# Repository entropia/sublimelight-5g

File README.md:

# sublimelight-5g

5th generation of illumination devices for Entropia e.V

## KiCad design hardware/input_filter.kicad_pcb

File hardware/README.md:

# sublimeilght-5g hardware

## known issues/gotchas

The pins in the footprint of the 3.3V regulator U5 are counted in the other direction compared to the 78-style regulators it replaces, but I used the 78-style kicad footprint there.
My solution was to replace the angeled pin header soldered to the module with a straight pin connector and then soldering U5 to the board so it points to the side of the PCB.
This also solves the possible issue that the levers of J8 aren't that far away from U5 when U5 is mounted at a 90 degree angle.

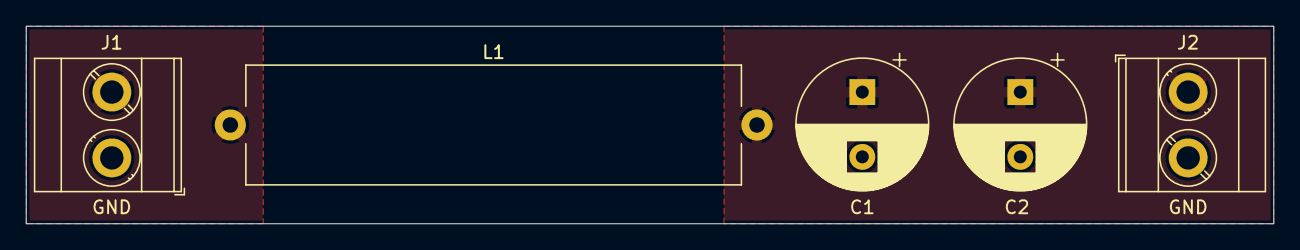
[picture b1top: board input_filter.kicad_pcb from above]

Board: 2 copper layers, 96.3 x 15.2 mm, 5 parts (0 on the bottom side), 3 nets, no tracks yet.

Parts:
C1, C2: EEU-FP1V511B; CP_Radial_D10.0mm_P5.00mm
J1, J2: Conn_01x02; TerminalBlock_Phoenix_MKDS-3-2-5.08_1x02_P5.08mm_Horizontal
L1: 5252-RC; R_Axial_Power_L38.0mm_W9.0mm_P40.64mm

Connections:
/V_IN: J1.2, L1.1
/V_OUT: C1.1, C2.1, J2.1, L1.2
GND: C1.2, C2.2, J1.1, J2.2

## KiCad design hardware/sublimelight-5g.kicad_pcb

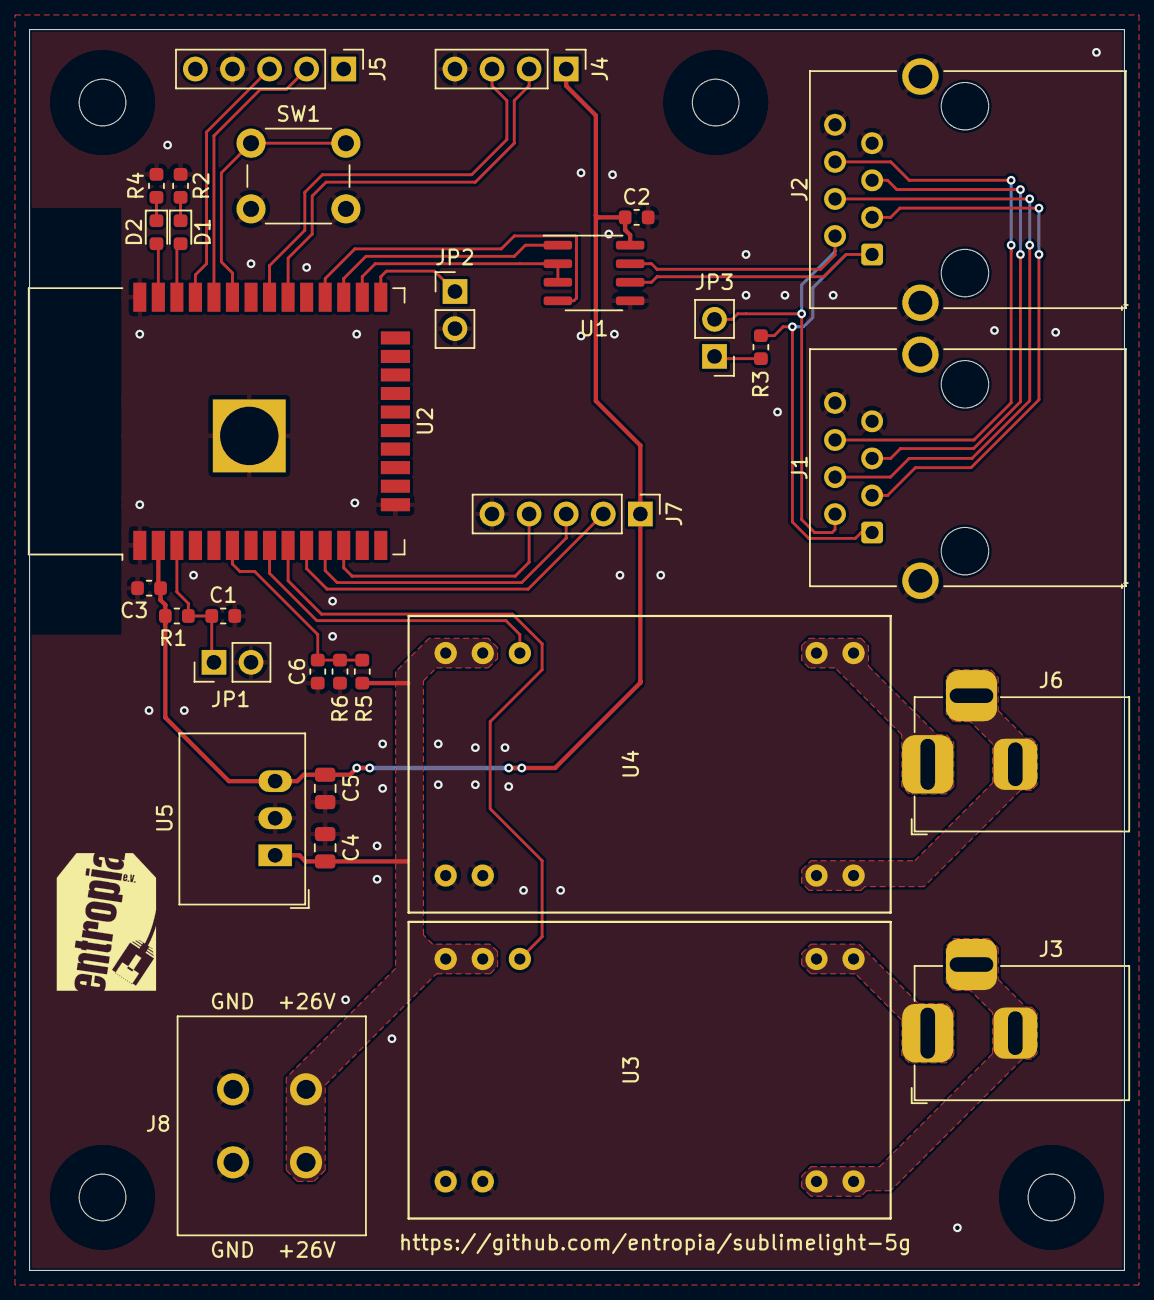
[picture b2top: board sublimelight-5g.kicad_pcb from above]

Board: 2 copper layers, 75.0 x 85.0 mm, 35 parts (0 on the bottom side), 34 nets.

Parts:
C1, C2, C3, C6: 100n; C_0603_1608Metric
C4: 10u; C_0805_2012Metric
C5: 22u; C_0805_2012Metric
D1, D2: LED; LED_0603_1608Metric
H1, H2, H3, H4: MountingHole; MountingHole_3.2mm_M3
J1, J2: RJ45; RJ45_MTJ-88TX1-FSD-PGB
J3, J6: Barrel_Jack_Switch; BarrelJack_Horizontal
J4: Conn_01x04; PinHeader_1x04_P2.54mm_Vertical
J5, J7: Conn_01x05; PinHeader_1x05_P2.54mm_Vertical
J8: Conn_01x02; TBL005A-500-02
JP1, JP2, JP3: Jumper_2_Open; PinHeader_1x02_P2.54mm_Vertical
R1, R6: 10k; R_0603_1608Metric
R2, R4: 1k; R_0603_1608Metric
R3: 120R; R_0603_1608Metric
R5: 100k; R_0603_1608Metric
SW1: SW_Push; SW_PUSH_6mm
U1: ST1480ACDR; SOIC-8_3.9x4.9mm_P1.27mm
U2: ESP32-WROOM-32D; ESP32-WROOM-32
U3, U4: LDD-H; LDD_H
U5: VXO7803-1000; Converter_DCDC_RECOM_R-78E-0.5_THT

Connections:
+3V3: C2.1, C3.1, C5.1, J4.1, J7.1, R1.1, U1.8, U2.2, U5.3
/AUX_0_0: J4.2, U2.30
/AUX_0_1: J4.3, U2.31
/AUX_1_0: J7.2, U2.10
/AUX_1_1: J7.3, U2.11
/AUX_1_2: J7.4, U2.12
/DI: U1.4, U2.28
/EN: C1.1, JP1.1, R1.2, U2.3
/IO0: JP2.1, U2.25
/LED0: D1.2, U2.36
/LED1: D2.2, U2.37
/PWM_W_COLD: U2.9, U3.22
/PWM_W_WARM: U2.8, U4.22
/RJ45_3: J1.3, J2.3
/RJ45_4: J1.4, J2.4
/RJ45_5: J1.5, J2.5
/RJ45_6: J1.6, J2.6
/RO: U1.1, U2.27
/RS485_A: J1.1, J2.1, R3.1, U1.6
/RS485_B: J1.2, J2.2, JP3.2, U1.7
/RTS: U1.2, U1.3, U2.26
/TASTER: SW1.1, U2.33
/USB_RXD: J5.3, U2.35
/USB_TXD: J5.2, U2.34
/V_SENSE: C6.1, R5.2, R6.1, U2.6
/W_COLD+: J3.1, U3.13, U3.14
/W_COLD-: J3.2, J3.3, U3.11, U3.12
/W_WARM+: J6.1, U4.13, U4.14
/W_WARM-: J6.2, J6.3, U4.11, U4.12
GND: C1.2, C2.2, C3.2, C4.2, C5.2, C6.2, J1.7, J1.8, J1.SH, J2.7, J2.8, J2.SH, J4.4, J5.4, J7.5, J8.1, JP1.2, JP2.2, R2.1, R4.1, R6.2, SW1.2, U1.5, U2.1, U2.15, U2.38, U2.39, U3.1, U3.2, U4.1, U4.2, U5.2
unnamed: D1.1, R2.2
unnamed: D2.1, R4.2
unnamed: JP3.1, R3.2
VCC: C4.1, J8.2, R5.1, U3.23, U3.24, U4.23, U4.24, U5.1

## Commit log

2019-10-19 add HW license
2019-10-19 move kicad gitignore to hardware folder
2019-10-19 add empty readme files
2019-10-19 add meanwell constant current led drivers
2019-10-19 create empty kicad project
2019-10-19 add meanwell constant current led driver to project
2019-10-20 add schematics backup file to gitignore
2019-10-20 begin hardware design
2019-10-20 add TBL005A-500-02 footprint
2019-10-24 add rj45 connector footprint
2019-10-24 first placement
2019-10-24 change net class parameters
2019-10-25 schematics mostly done; layout not finished yet
2019-10-26 route board
2019-10-26 add a little content to top-level readme
2019-10-26 add entropia logo
2019-10-26 add logo to board and clean up silkscreen
2019-10-29 sligthly change footprint of barel jack to match recommended footprint
2019-11-04 replace +28V power supply symbol with VCC symbol
    VCC is +26V
2019-11-16 add missing power flags in schematics
2019-11-16 add logos to board
2019-11-29 Imported Firmware-Skeleton
    From https://github.com/espressif/esp-idf-template.
2019-11-30 hardware/README.md: describe U5 problem/workaround
2020-01-01 Add LED test.
2020-01-01 Move test firmware to other directory, reset firmware to skeleton.
2020-01-02 Begin configuration web interface.
2020-01-05 WIP web interface.
2020-01-05 Update .gitignore for emacs.
2020-01-06 Finish web interface.
2020-01-06 Add necessary menuconfig adjustments.
2020-01-06 Add firmware update endpoint.
2020-01-07 Remove MQTT topic prefix setting, rename board_name -> device_name.
    We use the Tasmota convention for MQTT topics, so we simply include the
    device name in the topic.
2020-01-07 Remove default Wifi password.
2020-01-19 Hooray!
2020-02-21 Remove unneeded NULL check. free(NULL) is fine.
2020-02-21 Publish current IP address on stat/$device/IP.
2020-02-21 Delay rebooting after firmware update to enable HTTP response to be sent.
2020-02-21 Report git revision in web interface.
2020-02-22 Add prospective naming scheme.
2020-02-22 Add 3D model of power supply shroud (parameterized for both types of supply).
2020-02-28 hardware: add input LC denoise PCB
2020-03-01 Fix (?) generation of git_revision.h
2020-03-01 Honour configuration of broker URL instead of using hardcoded default.
    This means that after a config update we need to restart the MQTT client
    completely because we may need to connect to somewhere else. Given that
    config changes should be rare, we put no effort into restarting only when
    needed.
2020-03-01 Make fallback settings usably bright.
2020-03-05 Added publish functionality on light state change
2020-03-06 Fix memory leak and uninitialized local variable.
2020-03-09 Outsourced stat topic generation to topic_builder.c
2020-03-09 Remove obsolete variables
2020-03-09 Refactor MQTT receive handling to topic_builder
2020-03-21 Use statically allocated light_manager_state_t.
    Right now there is only ever one state object, so we have to need to
    allocate it on the heap.
2020-03-21 Make values in light_manager_state_t unsigned and not short.
    (a) It makes the types consistent with the API.
    (b) We don't need to save those four bytes.
2020-03-21 Add brightness and temperature settings to light_manager.
    This also requires more infrastructure to remember throwing all the
    required events. Withing the light manager, always use update_state_* to
    set values in the state. That will update the PWM module and post the
    correct event.
2020-03-21 Add auto_brightness setting to light_manager.
2020-04-04 Implement brightness/temperature commands and status updates in the MQTT client.
2020-05-09 Add link to reboot page to go back.
2020-05-22 Clamp all incoming values in light_manager.
2020-05-23 Store only device ID (without sl5g prefix) in NVS config.
    We need to change this because "sl5g" is a level on its own in the new
    topic scheme.
2020-05-23 Do not shorten CMND topics in the MQTT client, match against whole topic.
    In future, topics will be more complex and the topic builder needs to
    handle them completely.
2020-05-23 Move all topic handling from MQTT client to topic builder.
2020-05-23 Remove magic constants in topic builder.
2020-05-23 Remove verbose logging, implement BRIGHTNESS_AUTO in MQTT client.
2020-05-23 Fix temperature computation for BRIGHTNESS_AUTO.
2020-05-23 Implement ENABLE.
2020-05-23 Use new naming scheme for cmnd topics.
2020-05-23 Implement room name configuration.
2020-05-23 Implement room topics.
2020-08-15 Don't reimplement strndup.
2020-08-30 Avoid crash when DHCP address is lost.
    TODO: Check whether this always works and is the only problem.
2020-08-30 Add updater script.
2020-09-06 topic builder: free previous topics in rebuild_initial_topics.
    This is not harmful the first time it is called since "If ptr is NULL, no
    operation is performed." [man 3 free].
2020-09-06 Use global client handle rather than threading it through arguments.
    Who are we kidding here? There is only one MQTT client, might as well
    just access it directly.
2020-09-06 Make updater nicer with curses, and implement proper shutdown.
2020-09-06 Call topic builder directly from MQTT client, do not use events.
2020-09-12 Actually enable firmware updates.
2020-09-12 Simplify topic handler.
    1. We don't need to know whether a command was addressed to an individual
    panel or a room (or later a group). That means that it is enough to match
    on the last part that specifies the channel.
    2. We therefore do not need to keep the cmnd/... topic strings around to
    check against. We only build them to subscribe to them and then forget
    them.
2020-09-12 Add a script to test some MQTT commands.
2020-09-12 Fix subscribe_to_initial_topics: Subscribe to room/*room_name*/...
2020-09-12 clamp_double: Do not assume 0 will be in the interval.
2020-09-12 Add error handling to esp_mqtt_client_publish calls.
2020-09-12 Add configurable group handling.
    This is quite simple-minded as of now, see the TODO notes in
    set_group_membership.
2020-09-12 foreach_current_group_topic: Fix type warning.
2020-09-22 Fix power supply shroud dimensions.
2020-09-22 Updater: Fix typos.
2021-11-07 power-supply-shroud: thicker walls and third cable hole
